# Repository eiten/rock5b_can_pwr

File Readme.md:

# ROCK 5B High-Power CAN-Bus & Power HAT ("The Beast")

> 🌍 **Languages:** [English](Readme.md) | [Deutsch](Readme.de.md)

## Table of Contents

<!-- @import "[TOC]" {cmd="toc" depthFrom=1 depthTo=6 orderedList=false} -->

<!-- code_chunk_output -->

- [ROCK 5B High-Power CAN-Bus & Power HAT ("The Beast")](#rock-5b-high-power-can-bus--power-hat-the-beast)
  - [Table of Contents](#table-of-contents)
  - [About the Project](#about-the-project)
  - [Features & Technical Specifications](#features--technical-specifications)
    - [⚡ Power Distribution (Split-Path Architecture)](#-power-distribution-split-path-architecture)
    - [**🚀 Native CAN-Bus**](#-native-can-bus)
    - [🔌 Poka-Yoke Connectors](#-poka-yoke-connectors)
  - [Pinout](#pinout)
    - [J102 - TOOLHEAD (4-Pin Micro-Fit Square)](#j102---toolhead-4-pin-micro-fit-square)
    - [J103 - SPIDER / MCU (3-Pin Micro-Fit Row)](#j103---spider--mcu-3-pin-micro-fit-row)
    - [J_LCD - MONITOR (4-Pin Micro-Fit Row)](#j_lcd---monitor-4-pin-micro-fit-row)
  - [Status LEDs ("Mouse Cinema")](#status-leds-mouse-cinema)
  - [Software Configuration (Radxa OS / Armbian)](#software-configuration-radxa-os--armbian)
    - [1. Enable Overlay](#1-enable-overlay)
    - [2. Configure Interface](#2-configure-interface)
    - [3. Klipper Configuration](#3-klipper-configuration)
  - [Manufacturing Notes (BOM & PCB)](#manufacturing-notes-bom--pcb)
  - [License](#license)

<!-- /code_chunk_output -->

## About the Project

This HAT was developed to turn the **Radxa Rock 5B** into the ultimate control center for high-performance laser plotters and 3D printers (Klipper). It addresses the specific weaknesses of standard solutions:

1. **Stable Power Supply:** Delivers massive 5.2V/6A for the SBC and peripheral USB-C touchscreens.  
2. **Native CAN Performance:** Uses the integrated CAN controller of the RK3588 instead of slow SPI bridges.  
3. **Thermal Management:** A special "donut" design allows the CPU fan to draw fresh air through the PCB.

## Features & Technical Specifications

### ⚡ Power Distribution (Split-Path Architecture)

The board separates power paths for maximum safety and performance:

* **Input:** 24V DC via reverse-polarity protected **XT30 (High Current)** connector.  
* **High-Power Path (Laser/Toolhead):**  
  * Massive 3-layer copper connection.  
  * Direct 24V passthrough to toolhead (up to 120W+ possible, depending on power supply).  
  * Protected by **SMBJ24A TVS diode** against inductive voltage spikes (Back-EMF).  
* **Logic Path (SBC & Display):**  
  * Protected by **2A Fast** fuse (Littelfuse 0466 series, 63V rating).  
  * **DC/DC Converter:** TI **TPS56637** Synchronous Buck Converter.  
  * Output: **5.2V** (compensates for voltage drop on cables) at up to **6A**.

### **🚀 Native CAN-Bus**

* No USB adapters or SPI chips (MCP2515) required.  
* Uses the native **CAN1 Controller** of the RK3588 (Pins 32/33).  
* **Transceiver:** TI SN65HVD230 (3.3V Logic).  
* **ESD Protection:** NUP2105L diode on data lines.  
* **Termination:** 120Ω termination resistor switchable via solder jumper (JP1).

### 🔌 Poka-Yoke Connectors

Uses **Molex Micro-Fit 3.0** with different pin counts to physically prevent fatal miswiring (e.g., 24V to 5V input).

| Port | Type | Pins | Description |
| :---- | :---- | :---- | :---- |
| **24V IN** | **XT30** | 2 | Main input from power supply. |
| **TOOLHEAD** | **Micro-Fit** | 2x2 (4-Pin) | 24V High-Current + CAN data to laser/print head. |
| **CONTROLLER** | **Micro-Fit** | 1x3 (3-Pin) | Pure data connection to MCU mainboard (e.g., Spider). |
| **MONITOR** | **Micro-Fit** | 1x4 (4-Pin) | 2x 5.2V / 2x GND for powering external displays. |

## Pinout

### J102 - TOOLHEAD (4-Pin Micro-Fit Square)

*This is where the laser or print head is connected.*

1. **24V** (Unfused, High Power)  
2. **GND**  
3. **CAN_L**  
4. **CAN_H**

### J103 - SPIDER / MCU (3-Pin Micro-Fit Row)

*Connection to mainboard. Galvanically isolated from 24V.*

1. **GND**  
2. **CAN_L**  
3. **CAN_H**

### J_LCD - MONITOR (4-Pin Micro-Fit Row)

*Power supply for USB-C monitors or HDMI displays.*

1. **+5.2V**  
2. **+5.2V**  
3. **GND**  
4. **GND**

## Status LEDs ("Mouse Cinema")

The board features two labeled LEDs for quick diagnosis:

* 24V input present (fuse intact).  
* 5.2V logic voltage stable (Power Good signal from TPS56637).  

## Software Configuration (Radxa OS / Armbian)

Since the native CAN controller is used, setup is extremely simple.

### 1. Enable Overlay

Add the overlay for the CAN1 controller.  
Via rsetup:  
`Hardware -> Overlays -> Enable CAN1-M1 on GPIO3 (Pins 32/33)`.  
Manually (`/boot/extlinux/extlinux.conf`):  
Add `rk3588-can1-m1` to the `fdtoverlays` line.

### 2. Configure Interface

Create `/etc/network/interfaces.d/can0` for autostart:  
```
allow-hotplug can0 
iface can0 can static  
    bitrate 500000  
    up ip link set $IFACE txqueuelen 1024
```

### 3. Klipper Configuration

In printer.cfg:
```
[mcu]  
canbus_uuid: <your_uuid>  
# No more "serial:" entries!
```

## Manufacturing Notes (BOM & PCB)

* **PCB Specs:** 4-Layer (Signal / GND / Power / Signal), 1oz copper.  
* **GPIO Header:** A **Stacking Header (Extra Tall, min. 11mm spacer height)** is absolutely required to provide clearance from the CPU cooler.  
* **Soldering:** Due to massive ground and power planes, a preheater plate (printer heated bed) or preheating in an oven (100°C) is strongly recommended.

**Critical Components (LCSC):**

* Buck Converter: **TPS56637RPAR**  
* Inductor: **MDA1350-2R2M** (2.2µH, Isat > 15A, Shielded)  
* Transceiver: **SN65HVD230**  
* Fuse: **Littelfuse 0466002.NRHF** (2A, **63V Rating!**)

Disclaimer:  
This design works with high currents and voltages. Use at your own risk. Make sure cable cross-sections are rated for the load of your laser/hotend.

## License

This project is licensed under the **Creative Commons Attribution-NonCommercial-ShareAlike 4.0 International License** (CC BY-NC-SA 4.0).

This means you are free to:
- **Share** — copy and redistribute the material in any medium or format
- **Adapt** — remix, transform, and build upon the material

Under the following terms:
- **Attribution** — You must give appropriate credit, provide a link to the license, and indicate if changes were made
- **NonCommercial** — You may not use the material for commercial purposes
- **ShareAlike** — If you remix, transform, or build upon the material, you must distribute your contributions under the same license

For the full license text, visit: https://creativecommons.org/licenses/by-nc-sa/4.0/

---

> **Note:** The original documentation is in German ([Readme.de.md](Readme.de.md)). This English version is a translation for international users.

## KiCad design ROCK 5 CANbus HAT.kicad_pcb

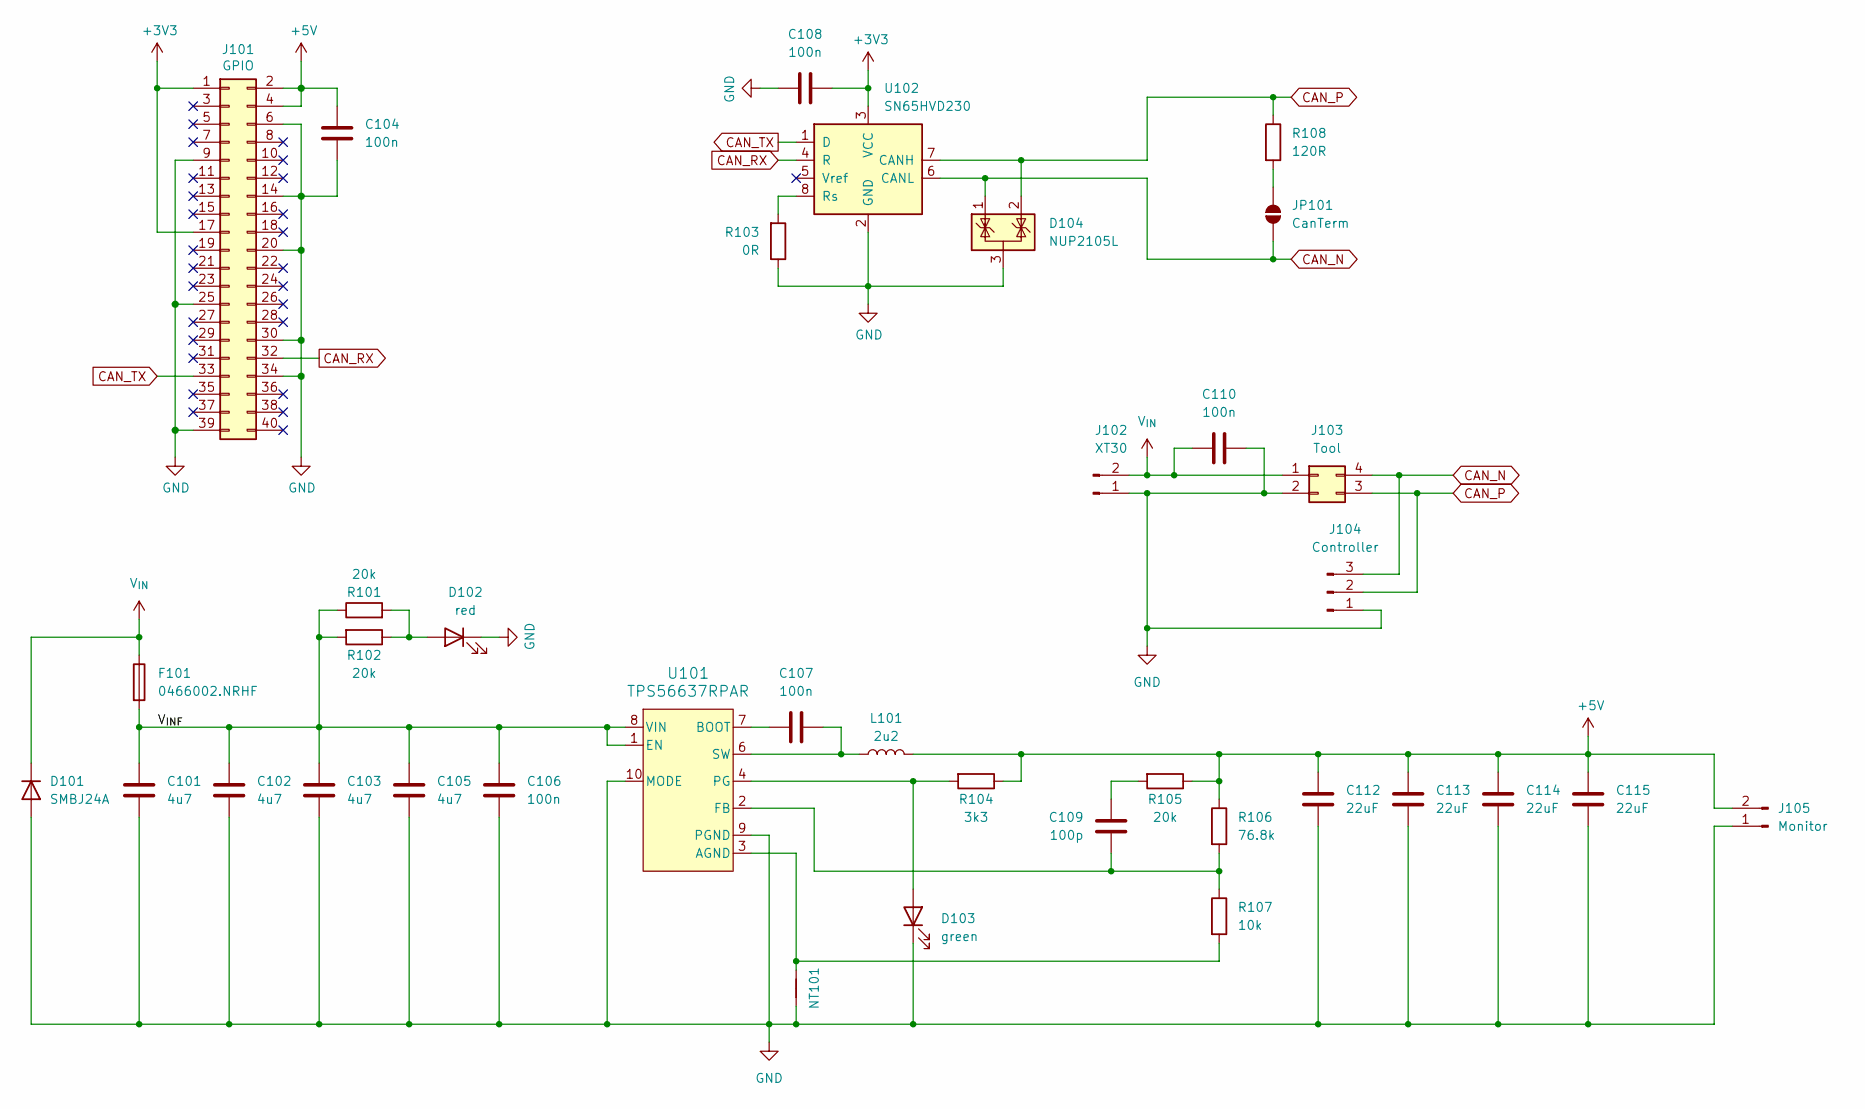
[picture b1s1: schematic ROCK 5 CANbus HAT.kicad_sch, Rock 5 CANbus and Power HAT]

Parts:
C101, C102, C103, C105: 4u7; C_1206_3216Metric; Manufacturer Part # 1206B475K500NT; LCSC Part # C29823
C104, C106, C107, C108, C110: 100n; C_0402_1005Metric; Manufacturer Part # CL05B104KO5NNNC; LCSC Part # C1525
C109: 100p; C_0402_1005Metric; Manufacturer Part # 0402CG101J500NT; LCSC Part # C1546
C112, C113, C114, C115: 22uF; C_1206_3216Metric; Manufacturer Part # CL31B226KPHNNNE; LCSC Part # C87996
D101: SMBJ24A; D_SMB; Manufacturer Part # SMBJ24A; LCSC Part # C224017
D102: red; LED_0805_2012Metric; Manufacturer Part # NCD0805R1; LCSC Part # C84256
D103: green; LED_0805_2012Metric; Manufacturer Part # KT-0805G; LCSC Part # C2297
D104: NUP2105L; SOT-23; Manufacturer Part # NUP2105LT1G; LCSC Part # C14486
F101: 0466002.NRHF; Fuse_1206_3216Metric; Manufacturer Part # 0466002.NRHF; LCSC Part # C3105
J101: GPIO; PinSocket_2x20_P2.54mm_Vertical; Manufacturer Part # C5307344; LCSC Part # C5307344
J102: XT30; AMASS_XT30PW-M_1x02_P2.50mm_Horizontal; Manufacturer Part # XT30PW-M30.G.Y; LCSC Part # C431092
J103: Tool; Molex_Micro-Fit_3.0_43045-0400_2x02_P3.00mm_Horizontal; Manufacturer Part # 430450400; LCSC Part # C122413
J104: Controller; Molex_Micro-Fit_3.0_43650-0300_1x03_P3.00mm_Horizontal; Manufacturer Part # 436500300; LCSC Part # C503478
J105: Monitor; Molex_Micro-Fit_3.0_43650-0200_1x02_P3.00mm_Horizontal; Manufacturer Part # 436500200; LCSC Part # C192562
JP101: CanTerm; SolderJumper-2_P1.3mm_Open_TrianglePad1.0x1.5mm
L101: 2u2; L_Changjiang_FXL1350; Manufacturer Part # MDA1350-2R2M; LCSC Part # C2847569
NT101: NetTie_2; NetTie-2_SMD_Pad0.5mm
R101, R102, R105: 20k; R_0402_1005Metric; Manufacturer Part # 0402WGF2002TCE; LCSC Part # C25765
R103: 0R; R_1206_3216Metric_Pad1.30x1.75mm_HandSolder; Manufacturer Part # 1206W4F0000T5E; LCSC Part # C17888
R104: 3k3; R_0402_1005Metric; Manufacturer Part # 0402WGF330KTCE; LCSC Part # C270612
R106: 76.8k; R_0402_1005Metric; Manufacturer Part # 0402WGF7682TCE; LCSC Part # C26987
R107: 10k; R_0402_1005Metric; Manufacturer Part # 0402WGF1200TCE; LCSC Part # 0402WGF1002TCE
R108: 120R; R_0402_1005Metric; Manufacturer Part # 0402WGF1200TCE; LCSC Part # C25079
U101: TPS56637RPAR; RPA0010A; Manufacturer Part # TPS56637RPAR; LCSC Part # C841386
U102: SN65HVD230; SOIC-8_3.9x4.9mm_P1.27mm; Manufacturer Part # SN65HVD230DR; LCSC Part # C12084

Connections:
+3V3: C108.2, J101.1, J101.17, U102.3 (VCC)
+5V: C104.2, C112.1, C113.1, C114.1, C115.1, J101.2, J101.4, J105.2, L101.2, R104.1, R105.1, R106.1
/V_{INF}: C101.1, C102.1, C103.1, C105.1, C106.1, F101.2, R101.1, R102.2, U101.1 (EN), U101.8 (VIN)
CAN_N: D104.1 (K), J103.4, J104.3, JP101.1 (A), U102.6 (CANL)
CAN_P: D104.2 (K), J103.3, J104.2, R108.1, U102.7 (CANH)
CAN_RX: J101.32, U102.4 (R)
CAN_TX: J101.33, U102.1 (D)
GND: C101.2, C102.2, C103.2, C104.1, C105.2, C106.2, C108.1, C110.1, C112.2, C113.2, C114.2, C115.2, D101.2 (A), D102.1 (K), D103.1 (K), D104.3 (A), J101.6, J101.9, J101.14, J101.20, J101.25, J101.30, J101.34, J101.39, J102.1, J103.2, J104.1, J105.1, NT101.2, R103.1, U101.9 (PGND), U101.10 (MODE), U102.2 (GND)
unnamed: C109.1, R105.2
unnamed: D102.2 (A), R101.2, R102.1
unnamed: D103.2 (A), R104.2, U101.4 (PG)
unnamed: JP101.2 (B), R108.2
unnamed: NT101.1, R107.2, U101.3 (AGND)
unnamed: C107.1, U101.7 (BOOT)
unnamed: C109.2, R106.2, R107.1, U101.2 (FB)
unnamed: C107.2, L101.1, U101.6 (SW)
unnamed: R103.2, U102.8 (Rs)
V_{IN}: C110.2, D101.1 (K), F101.1, J102.2, J103.1

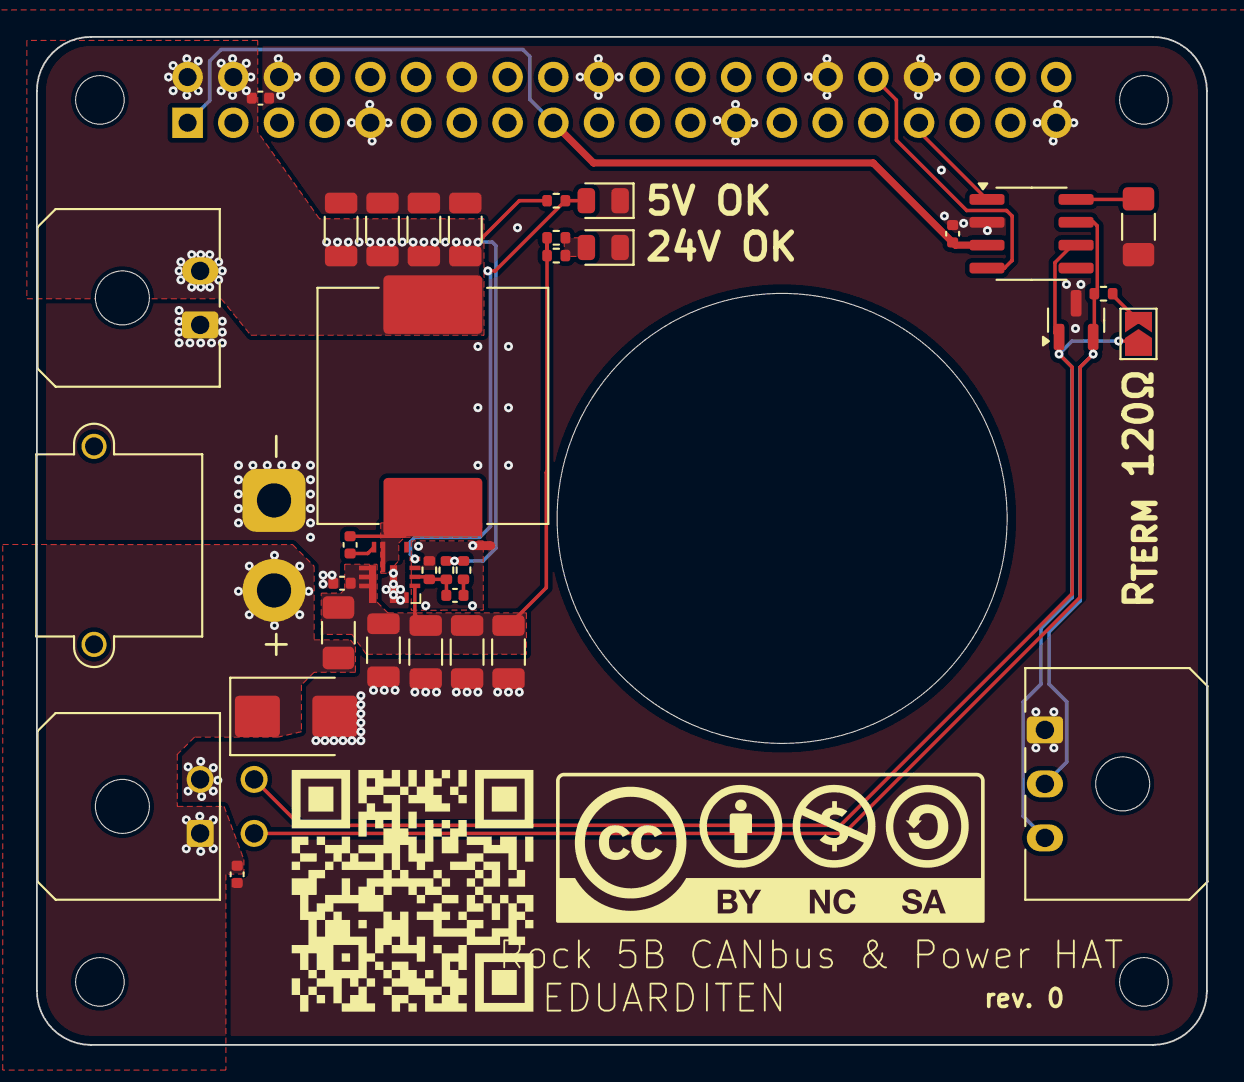
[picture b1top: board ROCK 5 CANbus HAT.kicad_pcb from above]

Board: 4 copper layers, 65.0 x 56.0 mm, 41 parts (1 on the bottom side), 18 nets.

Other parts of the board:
MH1, MH2, MH3, MH4: MountingHole_2.7mm_M2.5

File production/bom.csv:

Designator,Footprint,Quantity,Value,LCSC Part #
"C101, C102, C103, C105",1206,4,4u7,C29823
"C104, C106, C107, C108, C110",0402,5,100n,C1525
C109,0402,1,100p,C1546
"C112, C113, C114, C115",1206,4,22uF,C87996
D101,D_SMB,1,SMBJ24A,C224017
D102,0805,1,red,C84256
D103,0805,1,green,C2297
D104,SOT-23,1,NUP2105L,C14486
F101,1206,1,0466002.NRHF,C3105
J101,PinSocket_2x20_P2.54mm_Vertical,1,GPIO,C5307344
J102,AMASS_XT30PW-M_1x02_P2.50mm_Horizontal,1,XT30,C431092
J103,Molex_Micro-Fit_3.0_43045-0400_2x02_P3.00mm_Horizontal,1,Tool,C122413
J104,Molex_Micro-Fit_3.0_43650-0300_1x03_P3.00mm_Horizontal,1,Controller,C503478
J105,Molex_Micro-Fit_3.0_43650-0200_1x02_P3.00mm_Horizontal,1,Monitor,C192562
L101,L_Changjiang_FXL1350,1,2u2,C2847569
"R101, R102, R105",0402,3,20k,C25765
R103,1206,1,0R,C17888
R104,0402,1,3k3,C270612
R106,0402,1,76.8k,C26987
R107,0402,1,10k,0402WGF1002TCE
R108,0402,1,120R,C25079
U101,RPA0010A,1,TPS56637RPAR,C841386
U102,SOIC-8_3.9x4.9mm_P1.27mm,1,SN65HVD230,C12084

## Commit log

2025-11-23 Initial commit: Beast HAT rev. 0
2025-11-26 Add production files and update PCB layout
2025-11-26 Add language links and auto-generating table of contents
2025-11-26 Add CC BY-NC-SA 4.0 license and documentation notes
